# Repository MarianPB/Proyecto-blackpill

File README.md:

# Proyecto final

## Getting started

To make it easy for you to get started with GitLab, here's a list of recommended next steps.

Already a pro? Just edit this README.md and make it your own. Want to make it easy? [Use the template at the bottom](#editing-this-readme)!

## Add your files

* [Create](https://docs.gitlab.com/user/project/repository/web_editor/#create-a-file) or [upload](https://docs.gitlab.com/user/project/repository/web_editor/#upload-a-file) files
* [Add files using the command line](https://docs.gitlab.com/topics/git/add_files/#add-files-to-a-git-repository) or push an existing Git repository with the following command:

```
cd existing_repo
git remote add origin https://gitlab.com/proyectos5014538/proyecto-final.git
git branch -M main
git push -uf origin main
```

## Integrate with your tools

* [Set up project integrations](https://gitlab.com/proyectos5014538/proyecto-final/-/settings/integrations)

## Collaborate with your team

* [Invite team members and collaborators](https://docs.gitlab.com/user/project/members/)
* [Create a new merge request](https://docs.gitlab.com/user/project/merge_requests/creating_merge_requests/)
* [Automatically close issues from merge requests](https://docs.gitlab.com/user/project/issues/managing_issues/#closing-issues-automatically)
* [Enable merge request approvals](https://docs.gitlab.com/user/project/merge_requests/approvals/)
* [Set auto-merge](https://docs.gitlab.com/user/project/merge_requests/auto_merge/)

## Test and Deploy

Use the built-in continuous integration in GitLab.

* [Get started with GitLab CI/CD](https://docs.gitlab.com/ci/quick_start/)
* [Analyze your code for known vulnerabilities with Static Application Security Testing (SAST)](https://docs.gitlab.com/user/application_security/sast/)
* [Deploy to Kubernetes, Amazon EC2, or Amazon ECS using Auto Deploy](https://docs.gitlab.com/topics/autodevops/requirements/)
* [Use pull-based deployments for improved Kubernetes management](https://docs.gitlab.com/user/clusters/agent/)
* [Set up protected environments](https://docs.gitlab.com/ci/environments/protected_environments/)

***

# Editing this README

When you're ready to make this README your own, just edit this file and use the handy template below (or feel free to structure it however you want - this is just a starting point!). Thanks to [makeareadme.com](https://www.makeareadme.com/) for this template.

## Suggestions for a good README

Every project is different, so consider which of these sections apply to yours. The sections used in the template are suggestions for most open source projects. Also keep in mind that while a README can be too long and detailed, too long is better than too short. If you think your README is too long, consider utilizing another form of documentation rather than cutting out information.

## Name
Choose a self-explaining name for your project.

## Description
Let people know what your project can do specifically. Provide context and add a link to any reference visitors might be unfamiliar with. A list of Features or a Background subsection can also be added here. If there are alternatives to your project, this is a good place to list differentiating factors.

## Badges
On some READMEs, you may see small images that convey metadata, such as whether or not all the tests are passing for the project. You can use Shields to add some to your README. Many services also have instructions for adding a badge.

## Visuals
Depending on what you are making, it can be a good idea to include screenshots or even a video (you'll frequently see GIFs rather than actual videos). Tools like ttygif can help, but check out Asciinema for a more sophisticated method.

## Installation
Within a particular ecosystem, there may be a common way of installing things, such as using Yarn, NuGet, or Homebrew. However, consider the possibility that whoever is reading your README is a novice and would like more guidance. Listing specific steps helps remove ambiguity and gets people to using your project as quickly as possible. If it only runs in a specific context like a particular programming language version or operating system or has dependencies that have to be installed manually, also add a Requirements subsection.

## Usage
Use examples liberally, and show the expected output if you can. It's helpful to have inline the smallest example of usage that you can demonstrate, while providing links to more sophisticated examples if they are too long to reasonably include in the README.

## Support
Tell people where they can go to for help. It can be any combination of an issue tracker, a chat room, an email address, etc.

## Roadmap
If you have ideas for releases in the future, it is a good idea to list them in the README.

## Contributing
State if you are open to contributions and what your requirements are for accepting them.

For people who want to make changes to your project, it's helpful to have some documentation on how to get started. Perhaps there is a script that they should run or some environment variables that they need to set. Make these steps explicit. These instructions could also be useful to your future self.

You can also document commands to lint the code or run tests. These steps help to ensure high code quality and reduce the likelihood that the changes inadvertently break something. Having instructions for running tests is especially helpful if it requires external setup, such as starting a Selenium server for testing in a browser.

## Authors and acknowledgment
Show your appreciation to those who have contributed to the project.

## License
For open source projects, say how it is licensed.

## Project status
If you have run out of energy or time for your project, put a note at the top of the README saying that development has slowed down or stopped completely. Someone may choose to fork your project or volunteer to step in as a maintainer or owner, allowing your project to keep going. You can also make an explicit request for maintainers.

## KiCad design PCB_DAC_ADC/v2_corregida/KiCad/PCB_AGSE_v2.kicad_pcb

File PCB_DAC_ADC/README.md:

# PCB DAC + ADC (Black Pill + PCM3060)

Placa de una capa para fabricar por planchado de tóner. Proyectos de KiCad 10 que abren solos (huellas, símbolos
y modelo 3D incluidos). El firmware de la placa es `../Firmware_PCB`.

| Carpeta | Qué es |
|---|---|
| `v1_fabricada/` | La placa que se fabricó. **La huella de la Black Pill está mal** (columna izquierda invertida y columnas cambiadas de lado): no enchufar la Black Pill directo, usar el acople. |
| `acople_blackpill/` | Placa intermedia que corrige la v1: va entre la placa y la Black Pill, que queda girada 180° (USB hacia abajo) y corrida 7,62 mm. Ver `LEEME_acople.txt`. |
| `v2_corregida/` | Para rehacer la placa de cero: huella corregida y Black Pill girada 180°, sin acople y con el mismo firmware. No fabricada. Ver `LEEME_v2.txt`. |
| `3D/` | Modelo de la Black Pill que usan los tres proyectos. |
| `Guia_de_diseno_PCB.txt` | Criterios de diseño (masas, alimentación, reglas de fabricación artesanal) y el historial de la placa. |

En cada carpeta, `Planchado/` tiene el cobre para planchar (imprimir a tamaño real), la guía de armado y la
serigrafía. DRC sin errores en los tres proyectos.

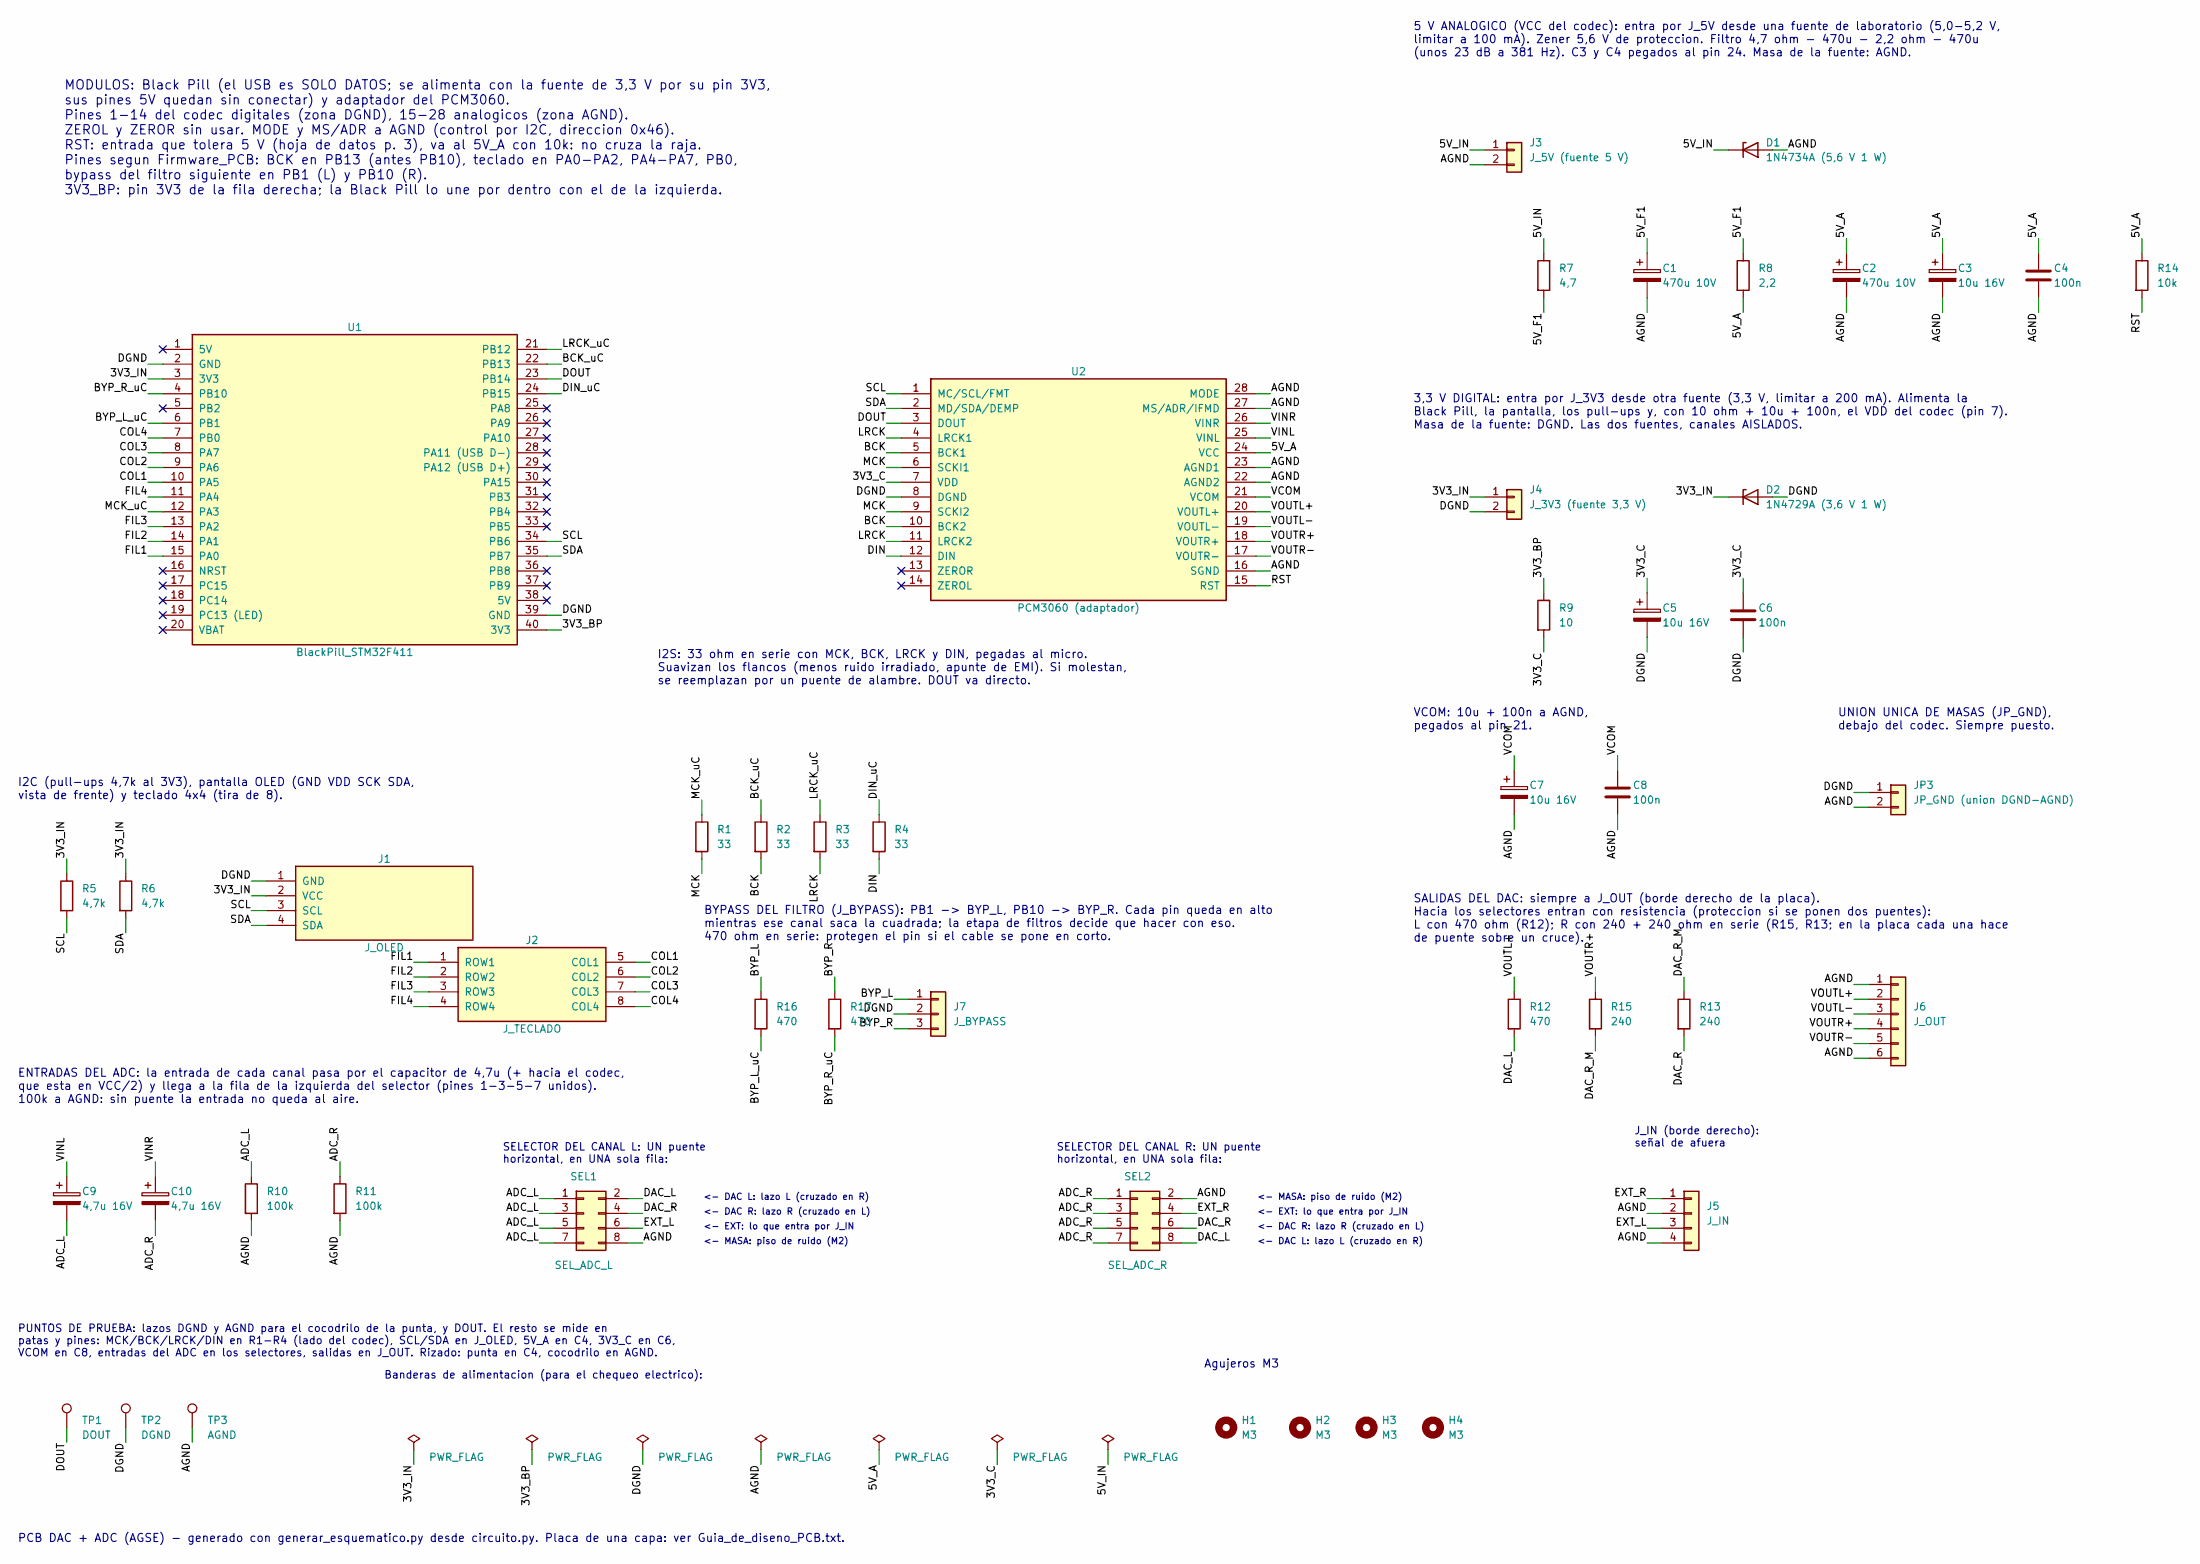
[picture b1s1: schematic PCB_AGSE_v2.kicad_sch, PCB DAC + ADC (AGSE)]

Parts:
C1, C2: 470u 10V; CP_Radial_D8.0mm_P3.50mm
C3, C5, C7: 10u 16V; CP_Radial_D5.0mm_P2.50mm
C4, C6, C8: 100n; C_Disc_D5.0mm_W2.5mm_P5.00mm
C9, C10: 4,7u 16V; CP_Radial_D5.0mm_P2.50mm
D1: 1N4734A (5,6 V 1 W); D_DO-41_SOD81_P10.16mm_Horizontal
D2: 1N4729A (3,6 V 1 W); D_DO-41_SOD81_P10.16mm_Horizontal
H1, H2, H3, H4: M3; MountingHole_3.2mm_M3
J1: J_OLED; PinHeader_1x04_P2.54mm_Vertical
J2: J_TECLADO; PinHeader_1x08_P2.54mm_Vertical
J3: J_5V (fuente 5 V); PinHeader_1x02_P2.54mm_Vertical
J4: J_3V3 (fuente 3,3 V); PinHeader_1x02_P2.54mm_Vertical
J5: J_IN; PinHeader_1x04_P2.54mm_Vertical
J6: J_OUT; PinHeader_1x06_P2.54mm_Vertical
J7: J_BYPASS; PinHeader_1x03_P2.54mm_Vertical
JP3: JP_GND (union DGND-AGND); PinHeader_1x02_P2.54mm_Vertical
R1, R2, R3, R4: 33; R_Axial_DIN0207_L6.3mm_D2.5mm_P10.16mm_Horizontal
R5, R6: 4,7k; R_Axial_DIN0207_L6.3mm_D2.5mm_P10.16mm_Horizontal
R7: 4,7; R_Axial_DIN0207_L6.3mm_D2.5mm_P10.16mm_Horizontal
R8: 2,2; R_Axial_DIN0207_L6.3mm_D2.5mm_P10.16mm_Horizontal
R9: 10; R_Axial_DIN0207_L6.3mm_D2.5mm_P10.16mm_Horizontal
R10, R11: 100k; R_Axial_DIN0207_L6.3mm_D2.5mm_P10.16mm_Horizontal
R12: 470; R_Axial_DIN0207_L6.3mm_D2.5mm_P10.16mm_Horizontal
R13, R15: 240; R_Axial_DIN0207_L6.3mm_D2.5mm_P10.16mm_Horizontal
R14: 10k; R_Axial_DIN0207_L6.3mm_D2.5mm_P10.16mm_Horizontal
R16, R17: 470; R_Axial_DIN0207_L6.3mm_D2.5mm_P5.08mm_Vertical
SEL1: SEL_ADC_L; PinHeader_2x04_P2.54mm_Vertical
SEL2: SEL_ADC_R; PinHeader_2x04_P2.54mm_Vertical
TP1: DOUT; TestPoint_Loop_D2.50mm_Drill1.0mm
TP2: DGND; TestPoint_Loop_D2.50mm_Drill1.0mm
TP3: AGND; TestPoint_Loop_D2.50mm_Drill1.0mm
U1: BlackPill_STM32F411; BlackPill_STM32F411_2x20
U2: PCM3060 (adaptador); PCM3060_Adaptador_DIP28_600mil

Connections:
/3V3_BP: R9.1, U1.40 (3V3)
/3V3_C: C5.1, C6.1, R9.2, U2.7 (VDD)
/3V3_IN: D2.1 (K), J1.2 (VCC), J4.1, R5.1, R6.1, U1.3 (3V3)
/5V_A: C2.1, C3.1, C4.1, R8.2, R14.1, U2.24 (VCC)
/5V_F1: C1.1, R7.2, R8.1
/5V_IN: D1.1 (K), J3.1, R7.1
/ADC_L: C9.2, R10.1, SEL1.1, SEL1.3, SEL1.5, SEL1.7
/ADC_R: C10.2, R11.1, SEL2.1, SEL2.3, SEL2.5, SEL2.7
/AGND: C1.2, C2.2, C3.2, C4.2, C7.2, C8.2, D1.2 (A), J3.2, J5.2, J5.4, J6.1, J6.6, JP3.2, R10.2, R11.2, SEL1.8, SEL2.2, TP3.1, U2.16 (SGND), U2.22 (AGND2), U2.23 (AGND1), U2.27 (MS/ADR/IFMD), U2.28 (MODE)
/BCK: R2.2, U2.5 (BCK1), U2.10 (BCK2)
/BCK_uC: R2.1, U1.22 (PB13)
/BYP_L: J7.1, R16.1
/BYP_L_uC: R16.2, U1.6 (PB1)
/BYP_R: J7.3, R17.1
/BYP_R_uC: R17.2, U1.4 (PB10)
/COL1: J2.5 (COL1), U1.10 (PA5)
/COL2: J2.6 (COL2), U1.9 (PA6)
/COL3: J2.7 (COL3), U1.8 (PA7)
/COL4: J2.8 (COL4), U1.7 (PB0)
/DAC_L: R12.2, SEL1.2, SEL2.8
/DAC_R: R13.2, SEL1.4, SEL2.6
/DAC_R_M: R13.1, R15.2
/DGND: C5.2, C6.2, D2.2 (A), J1.1 (GND), J4.2, J7.2, JP3.1, TP2.1, U1.2 (GND), U1.39 (GND), U2.8 (DGND)
/DIN: R4.2, U2.12 (DIN)
/DIN_uC: R4.1, U1.24 (PB15)
/DOUT: TP1.1, U1.23 (PB14), U2.3 (DOUT)
/EXT_L: J5.3, SEL1.6
/EXT_R: J5.1, SEL2.4
/FIL1: J2.1 (ROW1), U1.15 (PA0)
/FIL2: J2.2 (ROW2), U1.14 (PA1)
/FIL3: J2.3 (ROW3), U1.13 (PA2)
/FIL4: J2.4 (ROW4), U1.11 (PA4)
/LRCK: R3.2, U2.4 (LRCK1), U2.11 (LRCK2)
/LRCK_uC: R3.1, U1.21 (PB12)
/MCK: R1.2, U2.6 (SCKI1), U2.9 (SCKI2)
/MCK_uC: R1.1, U1.12 (PA3)
/RST: R14.2, U2.15 (RST)
/SCL: J1.3 (SCL), R5.2, U1.34 (PB6), U2.1 (MC/SCL/FMT)
/SDA: J1.4 (SDA), R6.2, U1.35 (PB7), U2.2 (MD/SDA/DEMP)
/VCOM: C7.1, C8.1, U2.21 (VCOM)
/VINL: C9.1, U2.25 (VINL)
/VINR: C10.1, U2.26 (VINR)
/VOUTL+: J6.2, R12.1, U2.20 (VOUTL+)
/VOUTL-: J6.3, U2.19 (VOUTL-)
/VOUTR+: J6.4, R15.1, U2.18 (VOUTR+)
/VOUTR-: J6.5, U2.17 (VOUTR-)

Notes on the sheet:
MODULOS: Black Pill (el USB es SOLO DATOS; se alimenta con la fuente de 3,3 V por su pin 3V3, sus pines 5V quedan sin conectar) y adaptador del PCM3060. Pines 1-14 del codec digitales (zona DGND), 15-28 analogicos (zona AGND). ZEROL y ZEROR sin usar. MODE y MS/ADR a AGND (control por I2C, direccion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
I2S: 33 ohm en serie con MCK, BCK, LRCK y DIN, pegadas al micro. Suavizan los flancos (menos ruido irradiado, apunte de EMI). Si molestan, se reemplazan por un puente de alambre. DOUT va directo.
BYPASS DEL FILTRO (J_BYPASS): PB1 -> BYP_L, PB10 -> BYP_R. Cada pin queda en alto mientras ese canal saca la cuadrada; la etapa de filtros decide que hacer con eso. 470 ohm en serie: protegen el pin si el cable se pone en corto.
I2C (pull-ups 4,7k al 3V3), pantalla OLED (GND VDD SCK SDA, vista de frente) y teclado 4x4 (tira de 8).
5 V ANALOGICO (VCC del codec): entra por J_5V desde una fuente de laboratorio (5,0-5,2 V, limitar a 100 mA). Zener 5,6 V de proteccion. Filtro 4,7 ohm - 470u - 2,2 ohm - 470u (unos 23 dB a 381 Hz). C3 y C4 pegados al pin 24. Masa de la fuente: AGND.
3,3 V DIGITAL: entra por J_3V3 desde otra fuente (3,3 V, limitar a 200 mA). Alimenta la Black Pill, la pantalla, los pull-ups y, con 10 ohm + 10u + 100n, el VDD del codec (pin 7). Masa de la fuente: DGND. Las dos fuentes, canales AISLADOS.
VCOM: 10u + 100n a AGND, pegados al pin 21.
UNION UNICA DE MASAS (JP_GND), debajo del codec. Siempre puesto.
SALIDAS DEL DAC: siempre a J_OUT (borde derecho de la placa). Hacia los selectores entran con resistencia (proteccion si se ponen dos puentes): L con 470 ohm (R12); R con 240 + 240 ohm en serie (R15, R13; en la placa cada una hace de puente sobre un cruce).
ENTRADAS DEL ADC: la entrada de cada canal pasa por el capacitor de 4,7u (+ hacia el codec, que esta en VCC/2) y llega a la fila de la izquierda del selector (pines 1-3-5-7 unidos). 100k a AGND: sin puente la entrada no queda al aire.
SELECTOR DEL CANAL L: UN puente horizontal, en UNA sola fila:
<- DAC L: lazo L (cruzado en R)
<- DAC R: lazo R (cruzado en L)
<- EXT: lo que entra por J_IN
<- MASA: piso de ruido (M2)
SELECTOR DEL CANAL R: UN puente horizontal, en UNA sola fila:
J_IN (borde derecho): señal de afuera
PUNTOS DE PRUEBA: lazos DGND y AGND para el cocodrilo de la punta, y DOUT. El resto se mide en patas y pines: MCK/BCK/LRCK/DIN en R1-R4 (lado del codec), SCL/SDA en J_OLED, 5V_A en C4, 3V3_C en C6, VCOM en C8, entradas del ADC en los selectores, salidas en J_OUT. Rizado: punta en C4, cocodrilo en A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
Agujeros M3
PCB DAC + ADC (AGSE) - generado con generar_esquematico.py desde circuito.py. Placa de una capa: ver Guia_de_diseno_PCB.txt.
Banderas de alimentacion (para el chequeo electrico):

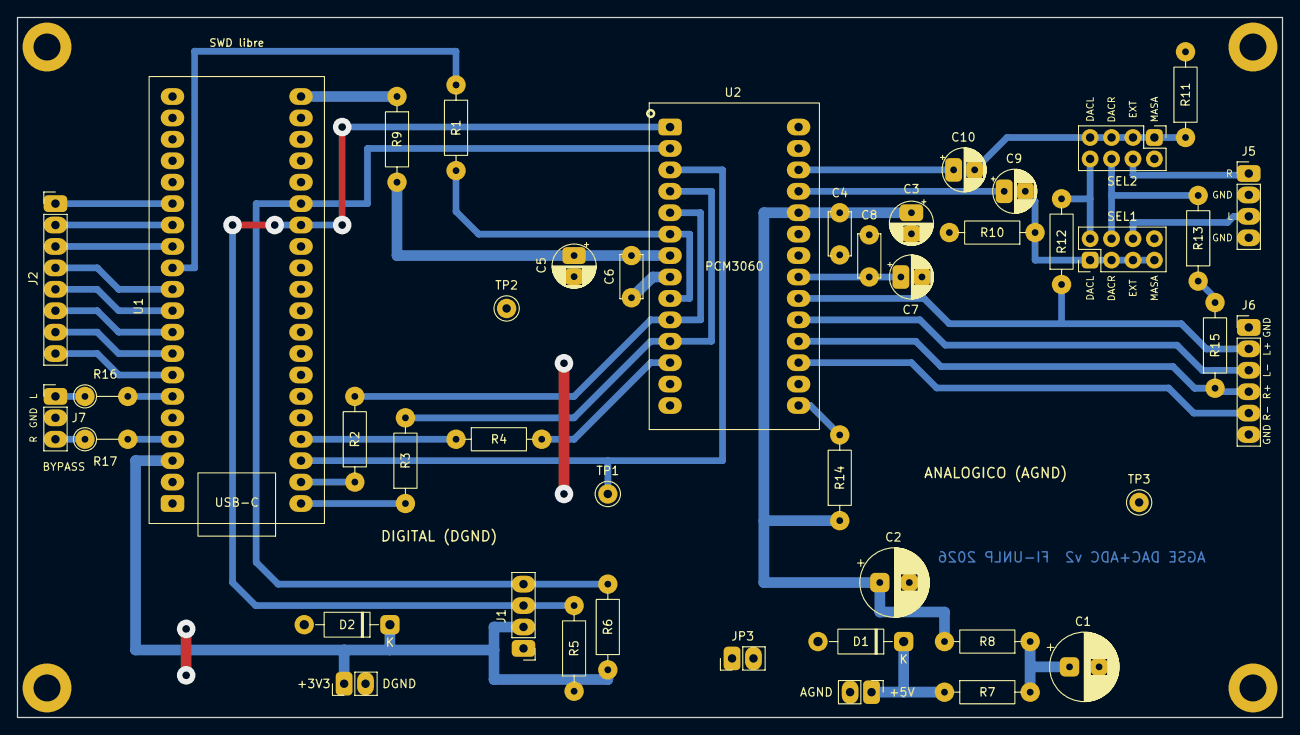
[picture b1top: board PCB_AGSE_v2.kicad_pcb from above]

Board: 2 copper layers, 150.0 x 83.0 mm, 48 parts (0 on the bottom side), 46 nets.

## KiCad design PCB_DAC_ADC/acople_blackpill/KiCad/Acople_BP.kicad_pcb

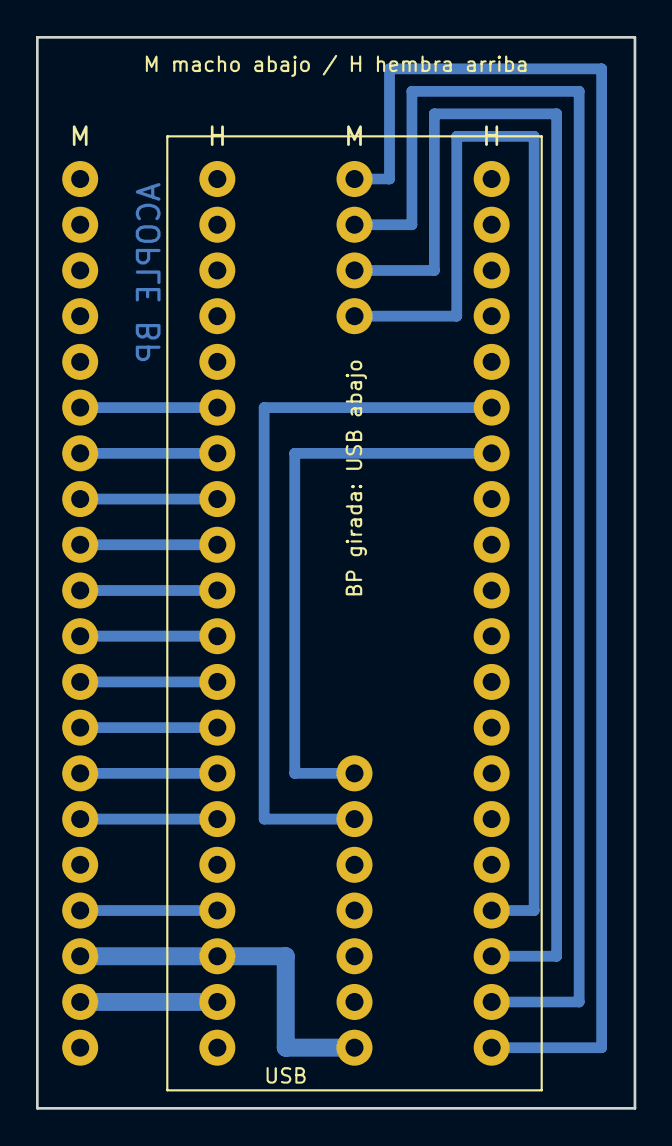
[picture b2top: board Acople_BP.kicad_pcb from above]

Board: 2 copper layers, 33.2 x 59.5 mm, 5 parts (0 on the bottom side), 19 nets.

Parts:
J1: PCB_izq_macho_1x20
J2: BP_izq_hembra_1x20
J3: PCB_der_macho_4+7
J4: BP_der_hembra_1x20
U1: BlackPill_STM32F411; BlackPill_girada

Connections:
3V3: J1.18, J2.18, J3.20
BCK_uC: J3.2, J4.19
BYP_L_uC: J1.15, J2.15
BYP_R_uC: J1.17, J2.17
COL1: J1.11, J2.11
COL2: J1.12, J2.12
COL3: J1.13, J2.13
COL4: J1.14, J2.14
DGND: J1.19, J2.19
DIN_uC: J3.4, J4.17
DOUT: J3.3, J4.18
FIL1: J1.6, J2.6
FIL2: J1.7, J2.7
FIL3: J1.8, J2.8
FIL4: J1.10, J2.10
LRCK_uC: J3.1, J4.20
MCK_uC: J1.9, J2.9
SCL: J3.14, J4.7
SDA: J3.15, J4.6

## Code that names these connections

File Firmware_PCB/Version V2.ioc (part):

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Mcu.Name=STM32F411C(C-E)Ux
Mcu.Package=UFQFPN48
Mcu.UserName=STM32F411CEUx
PA0-WKUP.GPIOParameters=PinState
PA0-WKUP.PinState=GPIO_PIN_SET
PA0-WKUP.Signal=GPIO_Output
PA1.GPIOParameters=PinState
PA1.PinState=GPIO_PIN_SET
PA1.Signal=GPIO_Output
PA11.Mode=Device_Only
PA11.Signal=USB_OTG_FS_DM
PA12.Mode=Device_Only
PA12.Signal=USB_OTG_FS_DP
PA13.Mode=Serial_Wire
PA13.Signal=SYS_JTMS-SWDIO
PA14.Mode=Serial_Wire
PA14.Signal=SYS_JTCK-SWCLK
PA2.GPIOParameters=PinState
PA2.PinState=GPIO_PIN_SET
PA2.Signal=GPIO_Output
PA3.Mode=Master_Clock_Activated
PA3.Signal=I2S2_MCK
PA4.GPIOParameters=PinState
PA4.PinState=GPIO_PIN_SET
PA4.Signal=GPIO_Output
PA5.GPIOParameters=GPIO_PuPd
PA5.GPIO_PuPd=GPIO_PULLUP
PA5.Signal=GPIO_Input
PA6.GPIOParameters=GPIO_PuPd
PA6.GPIO_PuPd=GPIO_PULLUP
PA6.Signal=GPIO_Input
PA7.GPIOParameters=GPIO_PuPd
PA7.GPIO_PuPd=GPIO_PULLUP
PA7.Signal=GPIO_Input
PB0.GPIOParameters=GPIO_PuPd
PB0.GPIO_PuPd=GPIO_PULLUP
PB0.Signal=GPIO_Input
PB1.GPIOParameters=GPIO_Label
PB1.GPIO_Label=BYP_L
PB1.Signal=GPIO_Output
PB10.GPIOParameters=GPIO_Label
PB10.GPIO_Label=BYP_R
PB10.Signal=GPIO_Output
PB12.Mode=Full_Duplex_Master
PB12.Signal=I2S2_WS
PB13.Mode=Full_Duplex_Master
PB13.Signal=I2S2_CK
PB14.Mode=Full_Duplex_Master
PB14.Signal=I2S2_ext_SD
PB15.Mode=Full_Duplex_Master
PB15.Signal=I2S2_SD
PB6.Mode=I2C
PB6.Signal=I2C1_SCL
PB7.Mode=I2C
PB7.Signal=I2C1_SDA
PH0\ -\ OSC_IN.Mode=HSE-External-Oscillator
PH0\ -\ OSC_IN.Signal=RCC_OSC_IN
PH1\ -\ OSC_OUT.Mode=HSE-External-Oscillator
PH1\ -\ OSC_OUT.Signal=RCC_OSC_OUT
RCC.HSE_VALUE=25000000
RCC.SYSCLKFreq_VALUE=96000000
RCC.SYSCLKSource=RCC_SYSCLKSOURCE_PLLCLK
board=custom
